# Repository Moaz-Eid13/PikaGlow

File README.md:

# PikaGlow
This is a design for a PCB that resembbles Pikachu the Beloved mascot of the Pokemon Franchise. As pikachu controllos electricity he will help in dark places and Light the way for you.
This Pcb utalizes an LDR to detect ambient ligt which will make two LEDs light in the dark and Turn off in the light.<br>

| Item No. | Part Name        | Quantity |
|----------|------------------|----------|
| 1  | Resistor 220Ω    | 2        |
| 2  | Capacitor 10uF   | 1        |
| 3  | CR2032 battery cell | 1     |
| 4  | Red 5mm LED      | 2        |
| 5  | photoresistor    | 1        |
| 6  | Resistor 47kΩ    | 1        |
|7   | 2N3904 transistor| 1        |
<br>
My Slack user name is Moaz Eid

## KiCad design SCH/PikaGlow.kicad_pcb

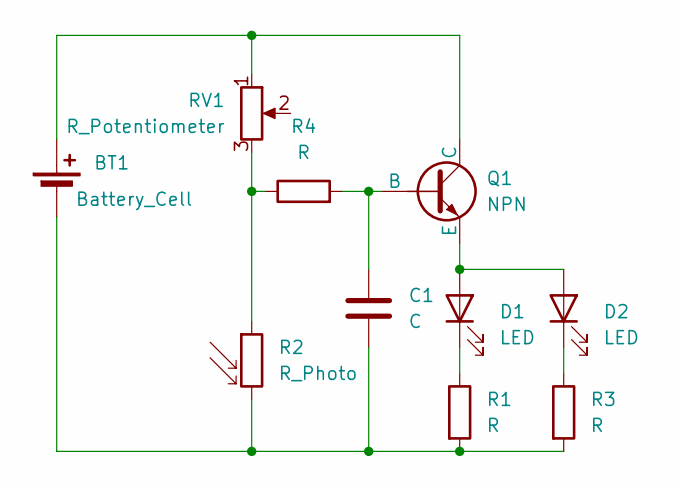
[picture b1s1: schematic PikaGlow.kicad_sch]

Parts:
BT1: Battery_Cell; BatteryHolder_Keystone_3034_1x20mm
C1: C; CP_Radial_D8.0mm_P5.00mm
D1, D2: LED; LED_D5.0mm
Q1: NPN; TO-92L_HandSolder
R1, R3, R4: R; R_Axial_DIN0207_L6.3mm_D2.5mm_P7.62mm_Horizontal
R2: R_Photo; R_LDR_5.1x4.3mm_P3.4mm_Vertical
RV1: R_Potentiometer; Potentiometer_Vishay_T73YP_Vertical

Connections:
unnamed: BT1.1 (+), Q1.1 (C), RV1.1
unnamed: BT1.2 (-), C1.2, R1.2, R2.2, R3.2
unnamed: D1.2 (A), D2.2 (A), Q1.3 (E)
unnamed: D1.1 (K), R1.1
unnamed: D2.1 (K), R3.1
unnamed: C1.1, Q1.2 (B), R4.2
unnamed: R2.1, R4.1, RV1.3

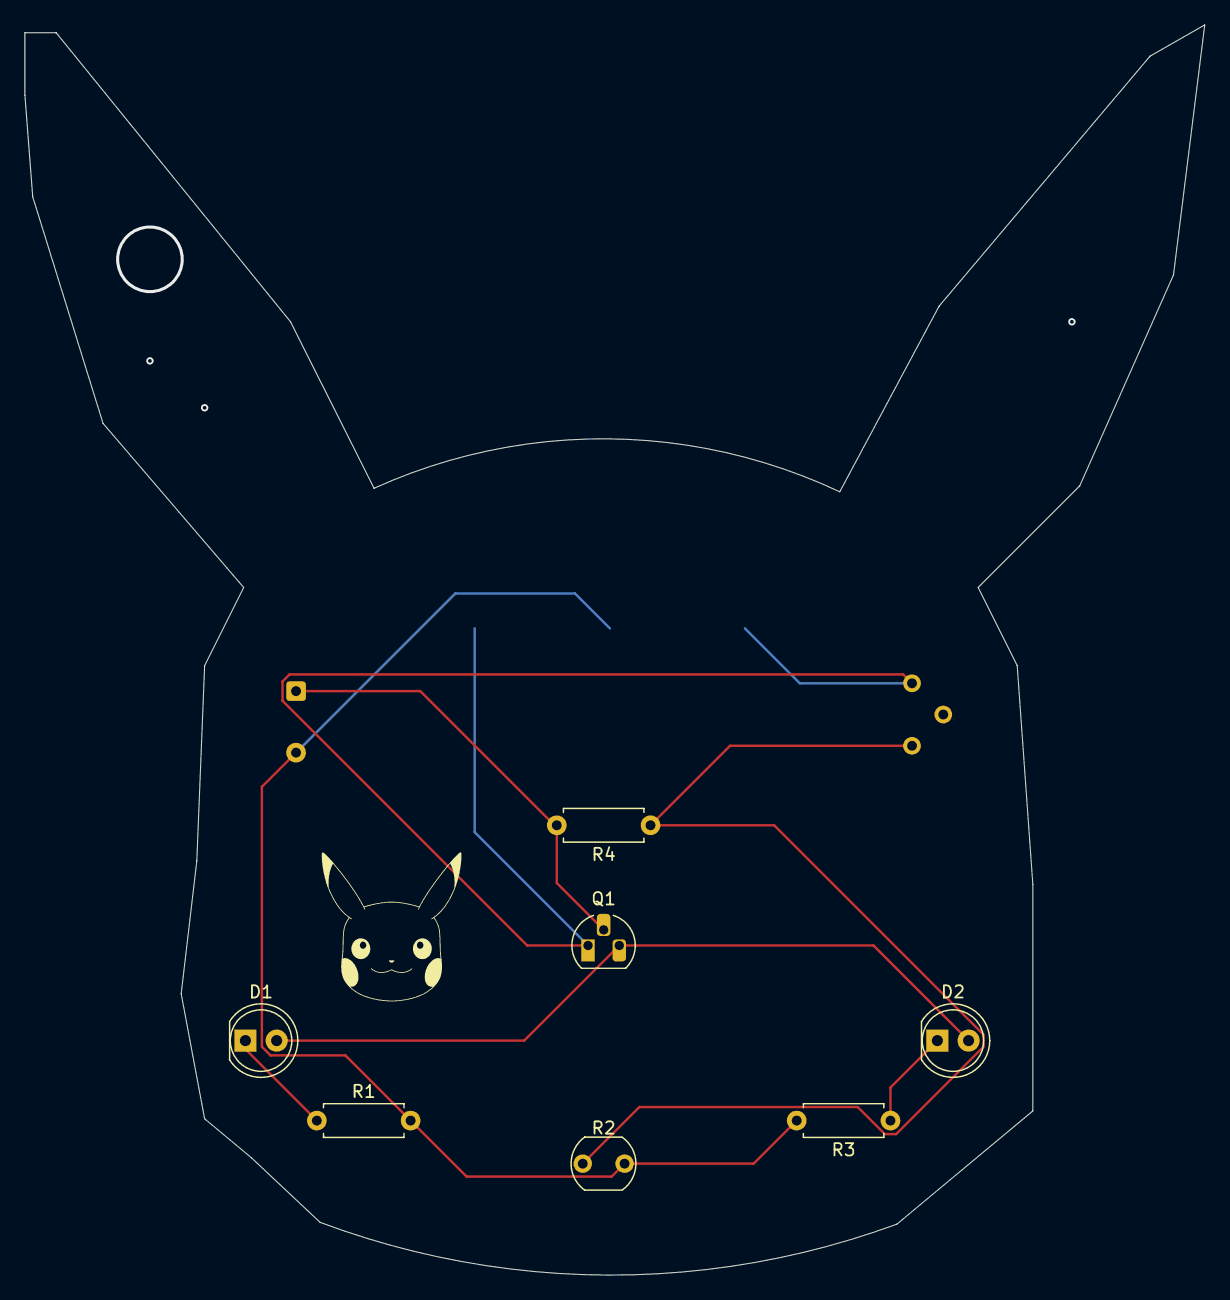
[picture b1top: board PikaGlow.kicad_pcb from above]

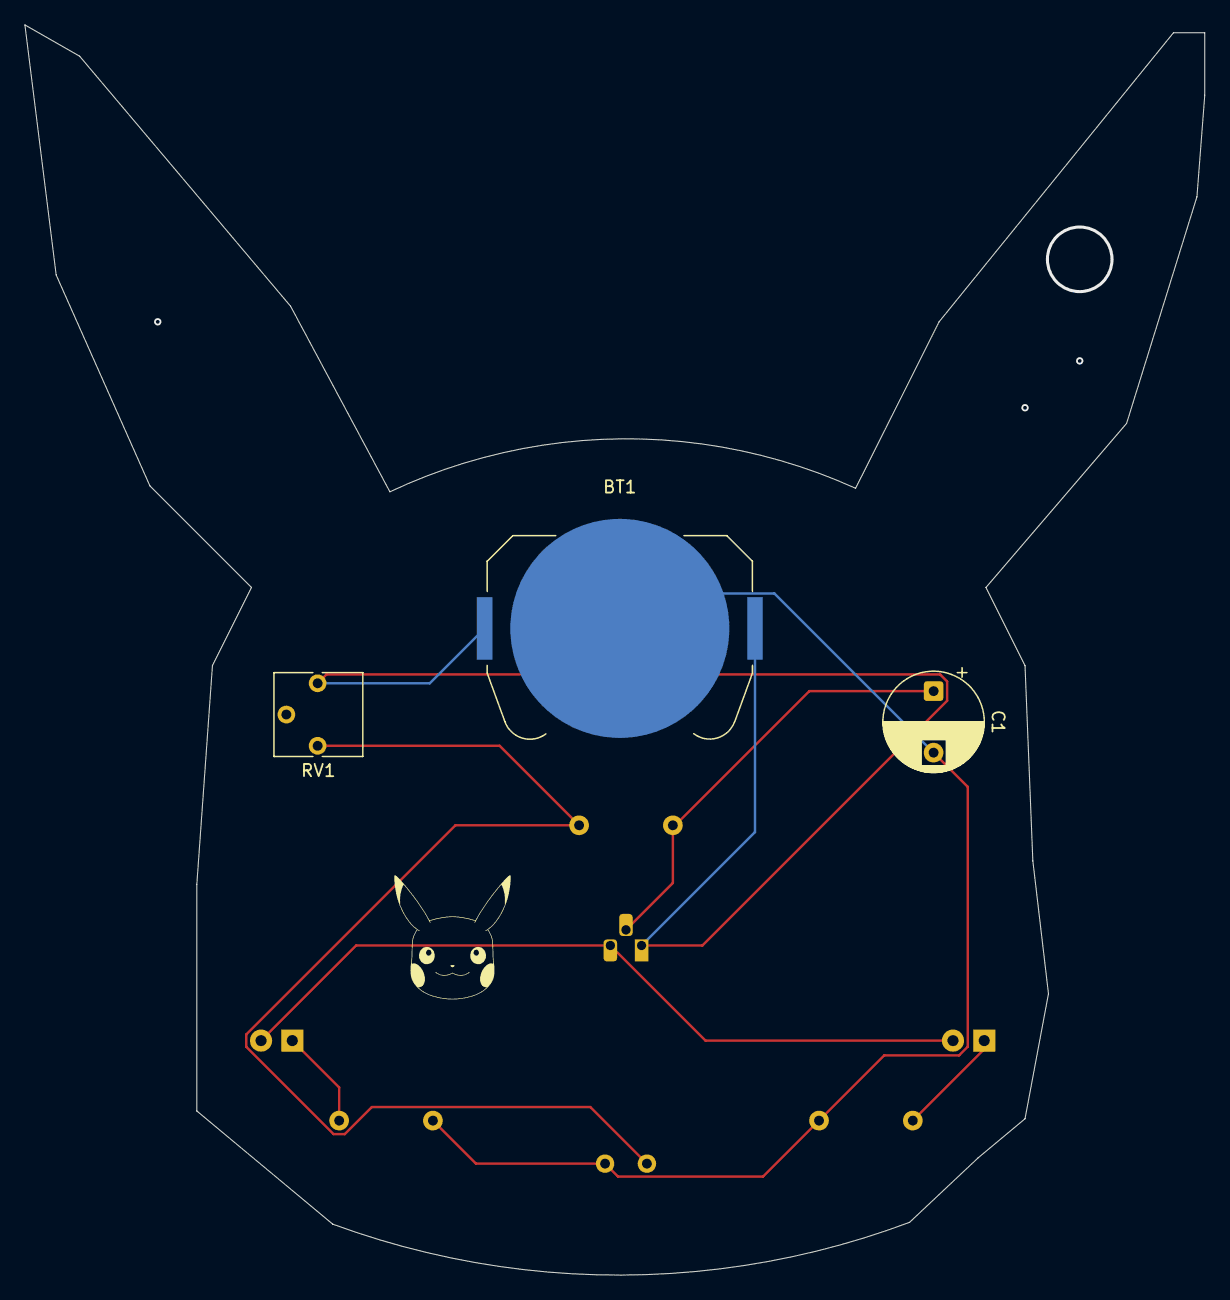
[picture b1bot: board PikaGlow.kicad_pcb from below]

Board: 2 copper layers, 95.9 x 101.6 mm, 10 parts (3 on the bottom side), 7 nets.

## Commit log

2025-06-24 README.md
2025-06-24 A custom PCB keychain
2025-06-24 A PCB keycain
2025-06-25 custom PCB
